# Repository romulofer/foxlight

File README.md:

# foxlight

Fotômetro refletido para fotografia analógica. Você define dois valores entre
**ISO**, **abertura** e **tempo**; o medidor calcula o terceiro.

| Versão | Cérebro | Para quê | Documentação |
| ------ | ------- | -------- | ------------ |
| Protoboard e **rev 1** | Wemos D1 mini (ESP8266) | bancada, alimentação por USB | este arquivo e [montagem](docs/MONTAGEM.md) |
| **rev 2** | Seeed XIAO ESP32C6 | compacto, sapata da câmera, bateria | [docs/REV2.md](docs/REV2.md) |

O mesmo firmware serve as duas.

> [!WARNING]
> **Trabalho em progresso.** Use por sua conta e risco.
>
> | Parte | Situação |
> | ----- | -------- |
> | Firmware na D1 mini, em protoboard | tela, sensor e botões funcionando na primeira versão; a tela nova ainda não foi gravada nela |
> | Calibração contra um fotômetro de referência | **não feita**: não confie nas leituras para expor filme |
> | Firmware na XIAO ESP32C6 | **só compilado**, nunca rodou na placa |
> | Placas rev 1 e rev 2 | **nunca fabricadas**; passam no DRC, mas várias medidas de módulos são estimadas |
> | Caixa da rev 2 | **nunca impressa** |
> | Bateria e alimentação | **nunca montadas nem testadas** |

## Recursos

- Medição de luz refletida, sem difusor, com o sensor apontado para a cena.
- Calcula tempo, abertura ou ISO, em passos de 1/3 de stop.
- ISO 6 a 25600, f/1.0 a f/64, 30 s a 1/8000 (tempos mais longos também aparecem).
- Medição contínua enquanto o botão é segurado.
- Faixa estendida: ajusta a sensibilidade do sensor em luz forte e fraca.
- Lux e EV na tela; configurações salvas na memória.
- Na rev 2: dorme sozinho, acorda no botão Medir e mostra a carga da bateria.

## Peças (protoboard)

Para a versão compacta, ver [docs/REV2.md](docs/REV2.md#peças).

| Qtd | Peça |
| --- | ---- |
| 1 | Wemos D1 mini ou clone (HW-386, USB-C) |
| 1 | Sensor BH1750 (GY-302), sem difusor |
| 1 | OLED SSD1306 128x64 I2C, 0,96" |
| 5 | Botões táteis 6x6 mm |

Em protoboard, a alimentação é pelo USB da placa. A placa rev 1 tem lugar para
bateria (ver [Placa rev 1](#placa-rev-1)).

## Ligações (D1 mini)

**Guia ilustrado, um passo de cada vez: [docs/MONTAGEM.md](docs/MONTAGEM.md).**

| D1 mini | Liga em |
| ------- | ------- |
| 3V3 | VCC do OLED e do BH1750 |
| GND | GND do OLED, do BH1750, ADDR do BH1750 e um lado de cada botão |
| D1 | SCL do OLED e do BH1750 |
| D2 | SDA do OLED e do BH1750 |
| D5 | botão **Medir** |
| D6 | botão **+** |
| D7 | botão **−** |
| D3 | botão **Selecionar** |
| D4 | botão **Calcular** |

Cada botão fica entre o pino e o GND, sem resistor. Não segure **Selecionar**
nem **Calcular** ao ligar: D3 e D4 definem o modo de boot do ESP8266.

Confira a ordem dos pinos na serigrafia de cada módulo. No OLED usado aqui é
`VCC GND SCL SDA`; no GY-302 costuma ser `VCC GND SCL SDA ADDR`.

## Uso

| Botão | Ação |
| ----- | ---- |
| Medir | faz uma leitura; segurando, mede continuamente |
| Calcular | escolhe a incógnita: tempo → abertura → ISO |
| Selecionar (**OK** na rev 2) | troca qual dos dois valores definidos será alterado |
| + / − (**►** / **◄** na rev 2) | altera o valor selecionado em 1/3 de stop; segurando, repete |

De cima para baixo: EV (ISO 100), lux e bateria; os dois valores definidos, com o
selecionado destacado; o resultado em letras grandes; e a régua do valor
selecionado, com o anterior e o próximo. Mudar um valor recalcula na hora com a
última leitura. As configurações são salvas 2 s depois da última mudança.

Resultados fora da escala aparecem como `<1.0`, `>64`, `<6`, `>25600` ou
`<1/8000`. Exposições além de 30 s mostram o tempo (`64s`, `2.1m`, `2h`), sem
correção de reciprocidade.

## Compilar e gravar

D1 mini (para a XIAO ESP32C6, ver [docs/REV2.md](docs/REV2.md#gravar)):

```bash
arduino-cli core install esp8266:esp8266 --additional-urls http://arduino.esp8266.com/stable/package_esp8266com_index.json
arduino-cli lib install "Adafruit GFX Library" "Adafruit SSD1306" BH1750
arduino-cli compile --fqbn esp8266:esp8266:d1_mini src/foxlight
arduino-cli upload  --fqbn esp8266:esp8266:d1_mini -p /dev/ttyUSB0 src/foxlight
```

Para conferir a montagem:

- `tools/i2c_scan` lista o barramento: devem aparecer `0x23` e `0x3C` (serial a 115200).
- `tools/button_test` mostra na tela o estado de cada botão.

Testes da matemática, no PC:

```bash
g++ -std=c++11 -Wall -Wextra -o /tmp/exposure_test test/exposure_test.cpp && /tmp/exposure_test
```

## Cálculo

```
EV100 = log2(lux * 100 / (Ω * K))      Ω = 2,53 sr, K = 12,5
abertura + tempo = EV100 + ISO         (escala APEX, em terços de stop)
```

- `K` é a constante de fotômetro refletido (ISO 2720).
- `Ω` é o ângulo sólido efetivo do BH1750 nu, obtido integrando as curvas de
  direcionalidade do [datasheet](https://wemos-docs.readthedocs.io/en/latest/_static/files/bh1750fvi-tr.pdf)
  (figs. 4 e 5).
- Isso supõe uma cena uniforme preenchendo o campo do sensor.

A fórmula `log2(lux / 2,5)`, comum em projetos com BH1750, é a de luz
**incidente**. Com o sensor apontado para a cena ela erra em cerca de 3 stops.

## Limitações

- Campo de visão muito largo (resposta cai à metade perto de ±50°). Céu ou uma
  lâmpada na borda alteram a leitura. Aproxime-se do assunto ou incline o
  aparelho um pouco para baixo. Um tubo na frente do sensor estreita o campo,
  mas exige recalibrar.
- O datasheet admite ±20% de variação entre sensores (cerca de 0,3 stop), e a
  resposta muda com o tipo de lâmpada.
- Não mede flash.
- A carga da bateria (só na rev 2) é uma estimativa pela tensão.

## Calibração

1. Aponte o foxlight e uma câmera com fotômetro para a mesma parede lisa, bem
   iluminada por igual, preenchendo o campo dos dois.
2. Use o mesmo ISO e abertura e compare os tempos.
3. Se o foxlight indicar um tempo N stops **mais rápido** que a câmera, use
   `CALIBRATION = 2^-N`; se mais lento, `2^N`. Em terços: 0,79 / 1,26.
4. Edite `CALIBRATION` em `src/foxlight/foxlight.ino` e grave de novo.

## Placa rev 1

| Frente | Verso |
| :----: | :---: |
|  |  |

*Imagens geradas pelo KiCad. Os módulos sem modelo 3D aparecem só como contorno.*

Projeto KiCad em [`hardware/kicad_rev1/`](hardware/kicad_rev1/), dupla face, 75 x 100 mm,
só componentes THT. Frente: tela e botões. Verso: sensor, D1 mini, bateria,
carregador e conversor. Gerbers em
[`hardware/foxlight_rev1_gerbers.zip`](hardware/foxlight_rev1_gerbers.zip).

> [!CAUTION]
> **Não mande fabricar sem conferir.** Contornos e furos do OLED, do GY-302 e do
> MT3608 foram estimados por foto. Imprima os moldes
> [da frente](hardware/imagens/rev1_molde_frente_1x1.pdf) e
> [do verso](hardware/imagens/rev1_molde_verso_1x1.pdf) em escala 100% e encoste os
> módulos no papel. Confira também o suporte da pilha.

| Ref | Peça |
| --- | ---- |
| U1 | Wemos D1 mini (2 barras fêmea 1x8, opcional) |
| J1 | OLED SSD1306 0,96" I2C |
| J2 | GY-302 BH1750 |
| J3 | Carregador de **500 mA com proteção** (por exemplo TP4057, pads B+ B− OUT+ OUT−), até 18 x 22 mm, preso com fita e ligado por fios |
| J4 | Elevador para 5 V: MT3608 soldado direto, ou módulo de saída fixa (até 17 x 22 mm) ligado por fios |
| J5 | Chave liga/desliga externa, 2 fios |
| BT1 | Suporte AA Keystone 2460 (51,99 mm entre pinos) + célula 14500 Li-ion |
| D1 | Diodo Schottky 1N5819 |
| R1 | Resistor 100 k (bateria no A0; o firmware ainda não lê) |
| SW1–SW5 | Botão tátil 6x6 mm, altura 9,5 mm |
| H1–H4 | Parafusos M3 |

### Montagem da parte de energia

Baterias de lítio podem pegar fogo se carregadas ou ligadas de forma errada.

1. **Use um carregador de 500 mA.** Os módulos TP4056 comuns carregam a 1 A,
   demais para uma 14500. O chip TP4057 é limitado a 500 mA: o CI principal tem
   6 pernas (SOT-23-6), e não 8 como o TP4056. O módulo precisa ter também o
   circuito de proteção (saídas OUT+ e OUT− separadas de B+ e B−). Há anúncios
   confusos, então **meça a corrente** na primeira carga.
2. **Confira os 5 V antes de encaixar o D1 mini.** Com a pilha, sem o D1 mini e
   com a chave ligada, meça OUT+ do conversor. No MT3608, gire o trimpot até
   5,0 V (ele pode sair com quase 30 V). Módulo de saída fixa só precisa ser
   medido.
3. **Não use o USB do conversor,** se ele tiver: está ligado direto na entrada.
4. **Chave desligada** ao ligar o USB do D1 mini e durante a carga.
5. Confira a polaridade da pilha. Invertida, pode queimar o carregador.

## Estrutura

```
src/foxlight/     firmware (foxlight.ino), pinos (board.h), exposição e bateria
test/             testes da matemática, rodam no PC
docs/             guia de montagem na protoboard e documentação da rev 2
tools/            testes de bancada e geradores dos desenhos, da tela e da caixa
hardware/         projetos KiCad, gerbers, caixa 3D, imagens e moldes 1:1
```

## Referências

Projetos consultados para conferir os cálculos. Nenhum código deles está neste
repositório.

| Projeto | Consultado para |
| ------- | --------------- |
| [addrummond/mlm](https://github.com/addrummond/mlm) | conversão de lux para EV refletido |
| [m3_lightmeter](https://github.com/ScaredCube/m3_lightmeter) | pares de exposição como deslocamento em passos de stop |
| [oleksiikutuzov/flipperzero-lightmeter](https://github.com/oleksiikutuzov/flipperzero-lightmeter) | uso do BH1750 |
| [vpominchuk/lightmeter](https://github.com/vpominchuk/lightmeter) | referência de fotômetro com BH1750 |
| [Seeed-Studio/OPL_Kicad_Library](https://github.com/Seeed-Studio/OPL_Kicad_Library) | posição dos pinos e dos pads de bateria da XIAO |

O firmware usa as bibliotecas [BH1750](https://github.com/claws/BH1750),
Adafruit GFX e Adafruit SSD1306, cada uma sob a própria licença.

## Autor e licença

Autor: [Rômulo](https://github.com/romulofer).

Livre para uso **não comercial**, sob
[Creative Commons Attribution-NonCommercial 4.0](LICENSE) (CC BY-NC 4.0): pode
usar, modificar e compartilhar, citando o autor. Uso comercial só com
autorização.

Os footprints da biblioteca oficial do KiCad usados na placa seguem a licença
deles (CC BY-SA 4.0 com exceção para projetos).

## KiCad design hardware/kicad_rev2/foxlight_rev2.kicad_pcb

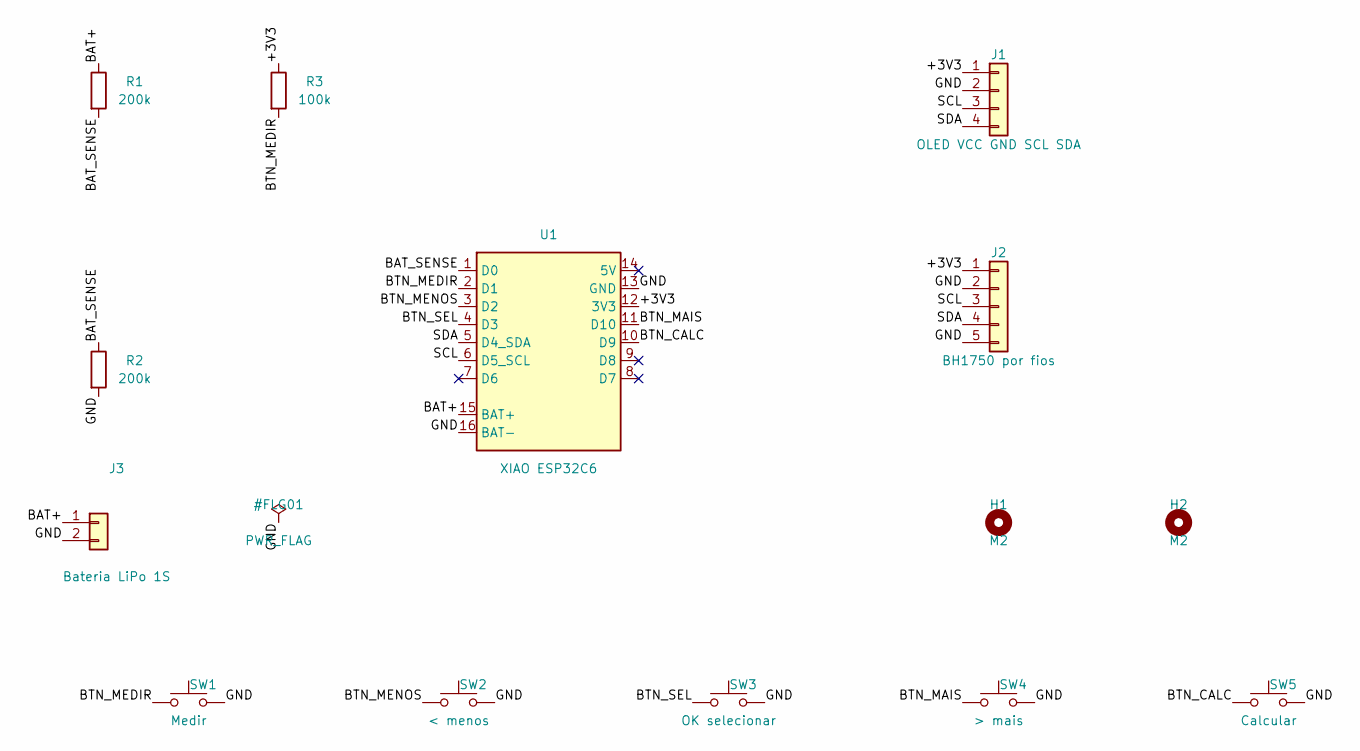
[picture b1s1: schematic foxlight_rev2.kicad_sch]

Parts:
H1, H2: M2; MountingHole_2.2mm_M2
J1: OLED VCC GND SCL SDA; OLED_SSD1306_096_I2C_Module
J2: BH1750 por fios; PinHeader_1x05_P2.54mm_Vertical
J3: Bateria LiPo 1S; PinHeader_1x02_P2.54mm_Vertical
R1, R2: 200k; R_Axial_DIN0207_L6.3mm_D2.5mm_P10.16mm_Horizontal
R3: 100k; R_Axial_DIN0207_L6.3mm_D2.5mm_P10.16mm_Horizontal
SW1: Medir; SW_Tactile_SPST_Angled_PTS645Vx83-2LFS
SW2: < menos; SW_Tactile_SPST_Angled_PTS645Vx83-2LFS
SW3: OK selecionar; SW_Tactile_SPST_Angled_PTS645Vx83-2LFS
SW4: > mais; SW_Tactile_SPST_Angled_PTS645Vx83-2LFS
SW5: Calcular; SW_Tactile_SPST_Angled_PTS645Vx83-2LFS
U1: XIAO ESP32C6; XIAO_ESP32C6_Pinos_Bateria

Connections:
/+3V3: J1.1, J2.1, R3.1, U1.12 (3V3)
/BAT+: J3.1, R1.1, U1.15 (BAT+)
/BAT_SENSE: R1.2, R2.1, U1.1 (D0)
/BTN_CALC: SW5.1, U1.10 (D9)
/BTN_MAIS: SW4.1, U1.11 (D10)
/BTN_MEDIR: R3.2, SW1.1, U1.2 (D1)
/BTN_MENOS: SW2.1, U1.3 (D2)
/BTN_SEL: SW3.1, U1.4 (D3)
/GND: J1.2, J2.2, J2.5, J3.2, R2.2, SW1.2, SW2.2, SW3.2, SW4.2, SW5.2, U1.13 (GND), U1.16 (BAT-)
/SCL: J1.3, J2.3, U1.6 (D5_SCL)
/SDA: J1.4, J2.4, U1.5 (D4_SDA)

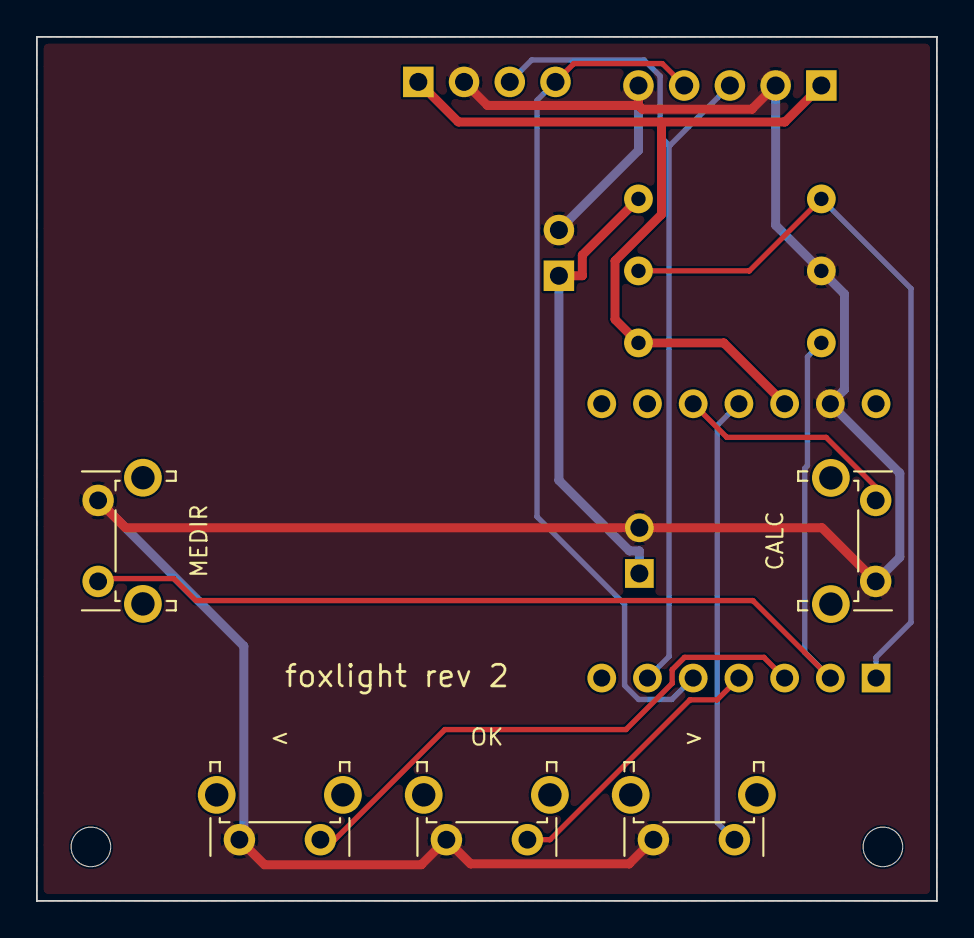
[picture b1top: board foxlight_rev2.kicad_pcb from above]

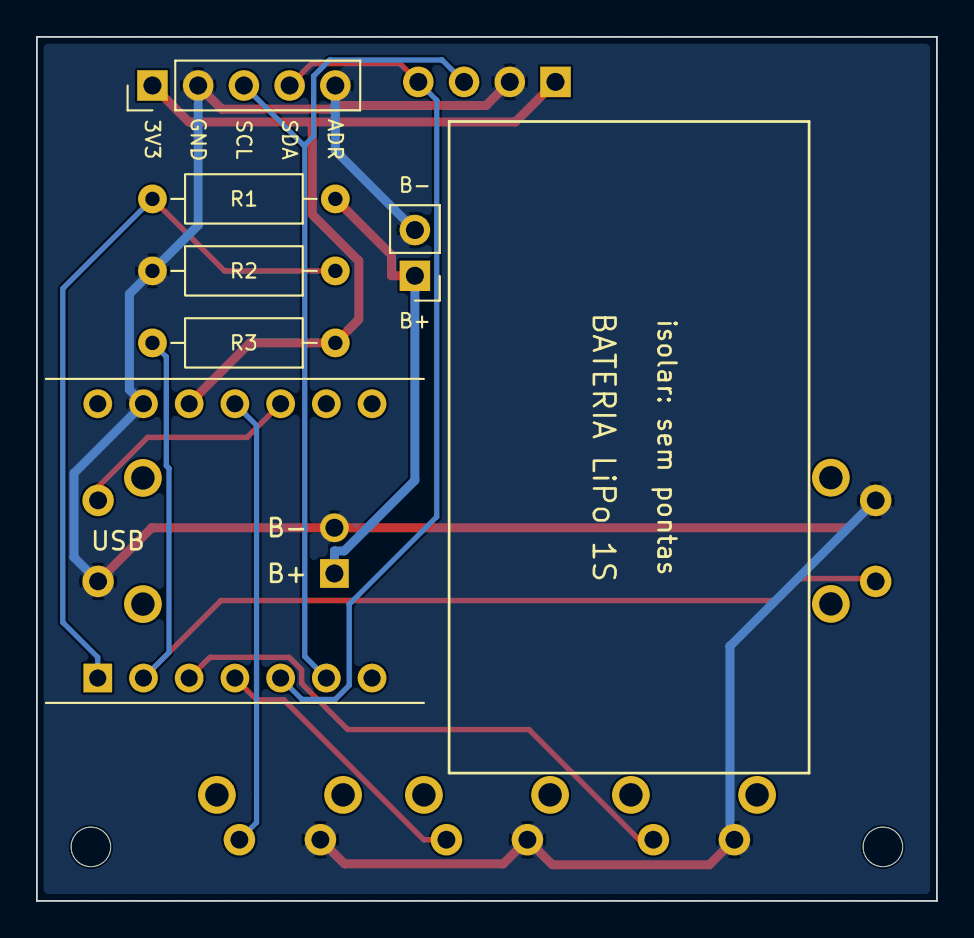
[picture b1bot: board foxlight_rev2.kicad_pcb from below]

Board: 2 copper layers, 50.0 x 48.0 mm, 14 parts (6 on the bottom side), 11 nets.

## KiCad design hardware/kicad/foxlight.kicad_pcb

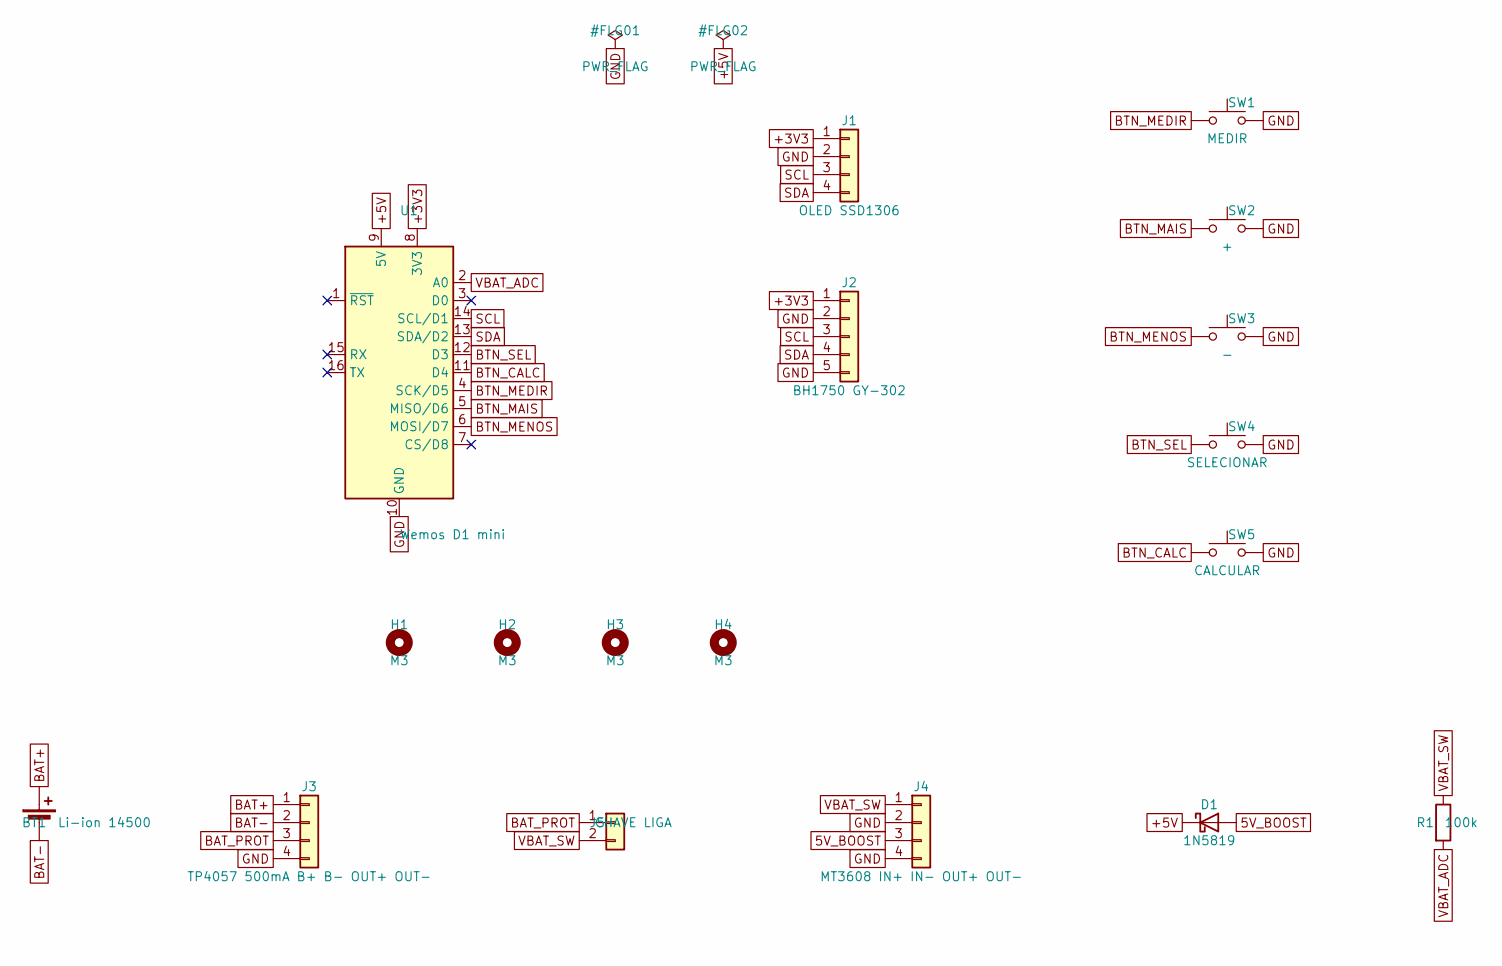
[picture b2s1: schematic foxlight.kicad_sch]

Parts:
BT1: Li-ion 14500; BatteryHolder_Keystone_2460_1xAA
D1: 1N5819; D_DO-41_SOD81_P10.16mm_Horizontal
H1, H2, H3, H4: M3; MountingHole_3.2mm_M3
J1: OLED SSD1306; OLED_SSD1306_096_I2C_Module
J2: BH1750 GY-302; BH1750_GY302_Module
J3: TP4057 500mA B+ B- OUT+ OUT-; Charger_Module_Universal_B_OUT
J4: MT3608 IN+ IN- OUT+ OUT-; MT3608_Boost_Module
J5: CHAVE LIGA; PinHeader_1x02_P2.54mm_Vertical
R1: 100k; R_Axial_DIN0207_L6.3mm_D2.5mm_P10.16mm_Horizontal
SW1: MEDIR; SW_PUSH_6mm_H9.5mm
SW2: +; SW_PUSH_6mm_H9.5mm
SW3: -; SW_PUSH_6mm_H9.5mm
SW4: SELECIONAR; SW_PUSH_6mm_H9.5mm
SW5: CALCULAR; SW_PUSH_6mm_H9.5mm
U1: Wemos D1 mini; WEMOS_D1_mini_light

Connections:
5V_BOOST: D1.2 (A), J4.3
+3V3: J1.1, J2.1, U1.8 (3V3)
+5V: D1.1 (K), U1.9 (5V)
BAT+: BT1.1 (+), J3.1
BAT-: BT1.2 (-), J3.2
BAT_PROT: J3.3, J5.1
BTN_CALC: SW5.1, U1.11 (D4)
BTN_MAIS: SW2.1, U1.5 (MISO/D6)
BTN_MEDIR: SW1.1, U1.4 (SCK/D5)
BTN_MENOS: SW3.1, U1.6 (MOSI/D7)
BTN_SEL: SW4.1, U1.12 (D3)
GND: J1.2, J2.2, J2.5, J3.4, J4.2, J4.4, SW1.2, SW2.2, SW3.2, SW4.2, SW5.2, U1.10 (GND)
SCL: J1.3, J2.3, U1.14 (SCL/D1)
SDA: J1.4, J2.4, U1.13 (SDA/D2)
VBAT_ADC: R1.2, U1.2 (A0)
VBAT_SW: J4.1, J5.2, R1.1

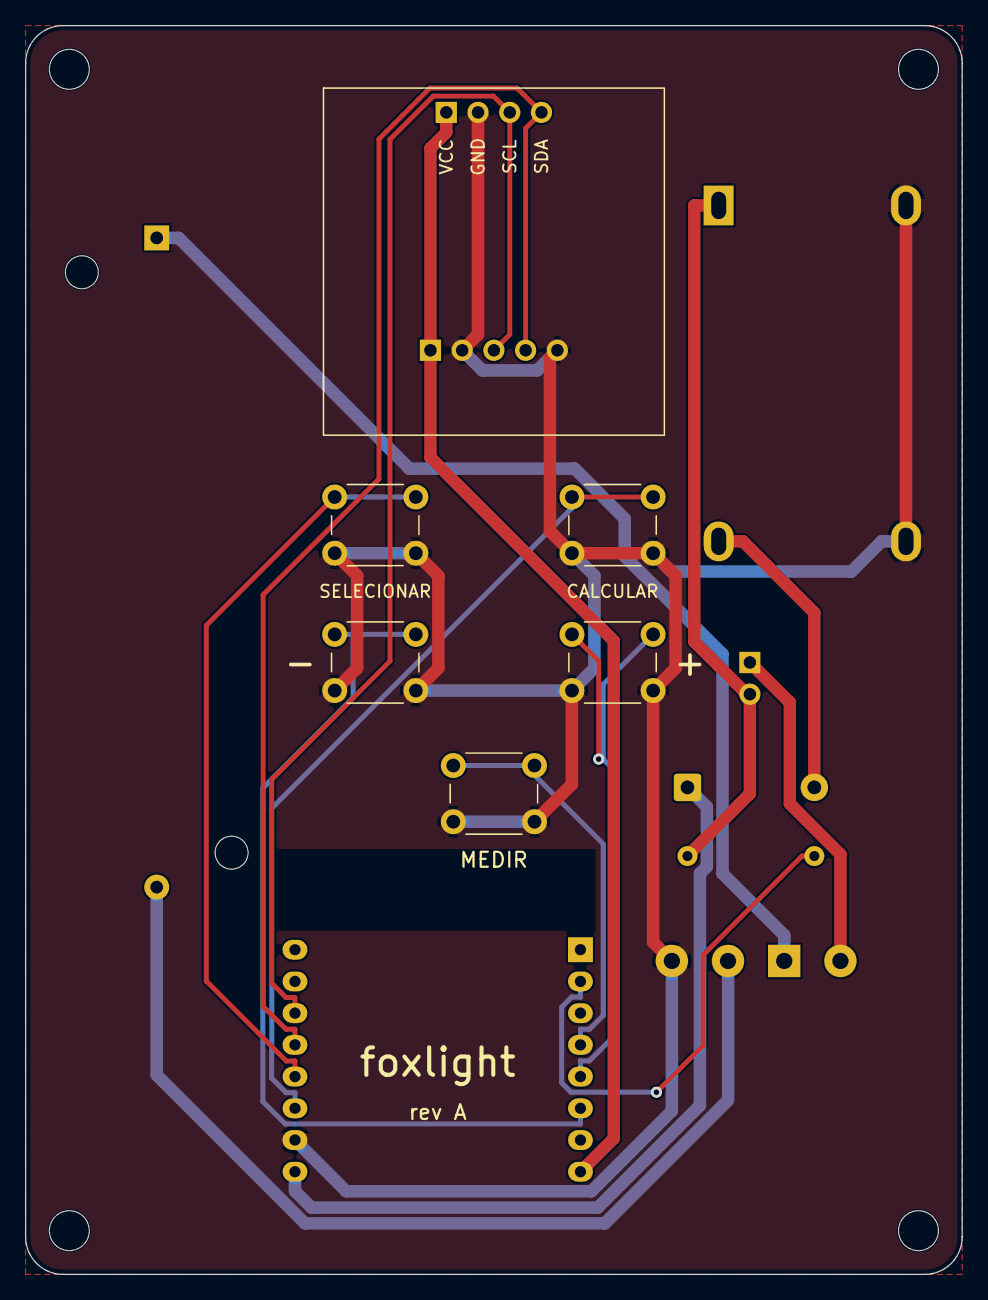
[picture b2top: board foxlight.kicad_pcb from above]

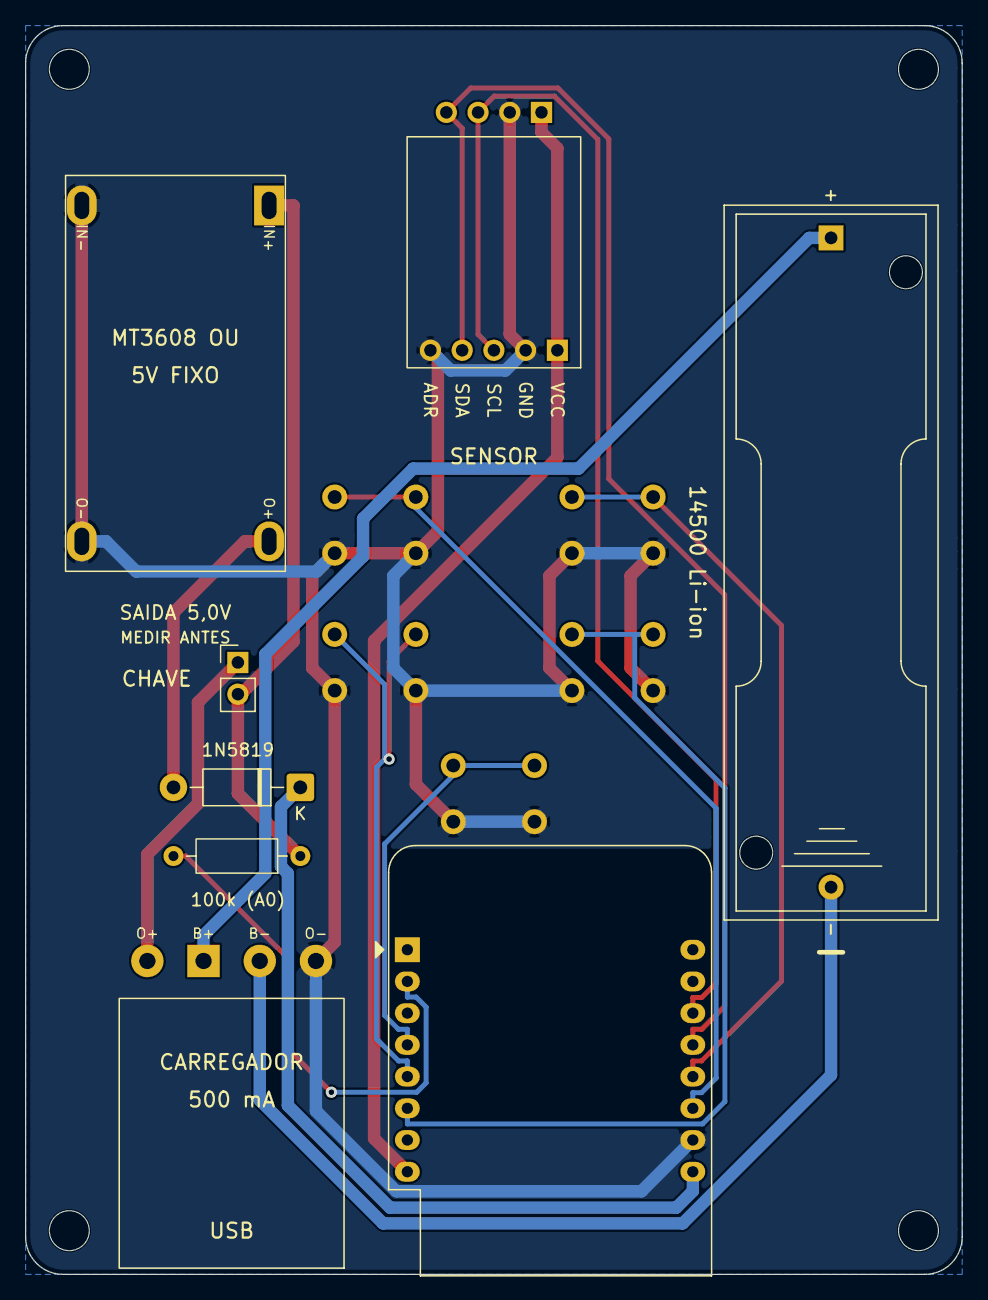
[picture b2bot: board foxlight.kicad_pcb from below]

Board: 2 copper layers, 75.0 x 100.0 mm, 18 parts (8 on the bottom side), 16 nets.
